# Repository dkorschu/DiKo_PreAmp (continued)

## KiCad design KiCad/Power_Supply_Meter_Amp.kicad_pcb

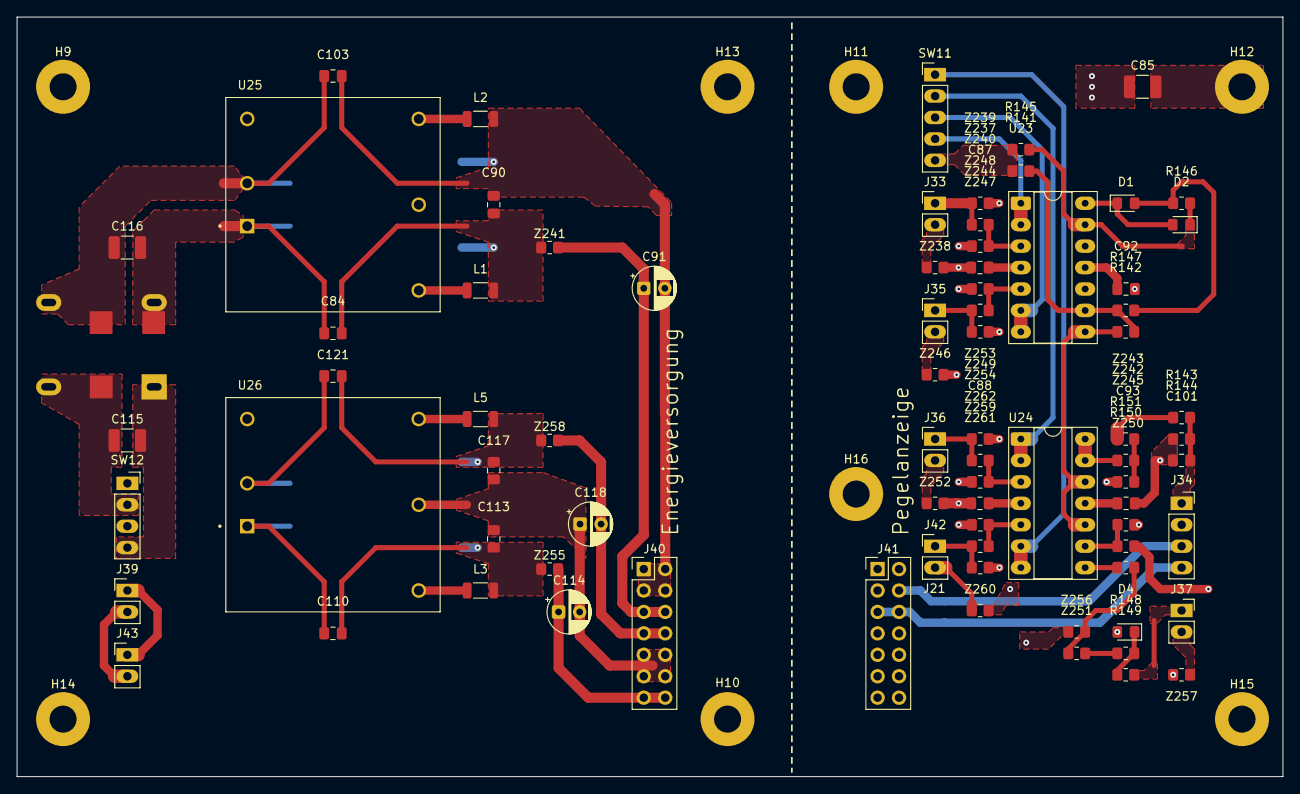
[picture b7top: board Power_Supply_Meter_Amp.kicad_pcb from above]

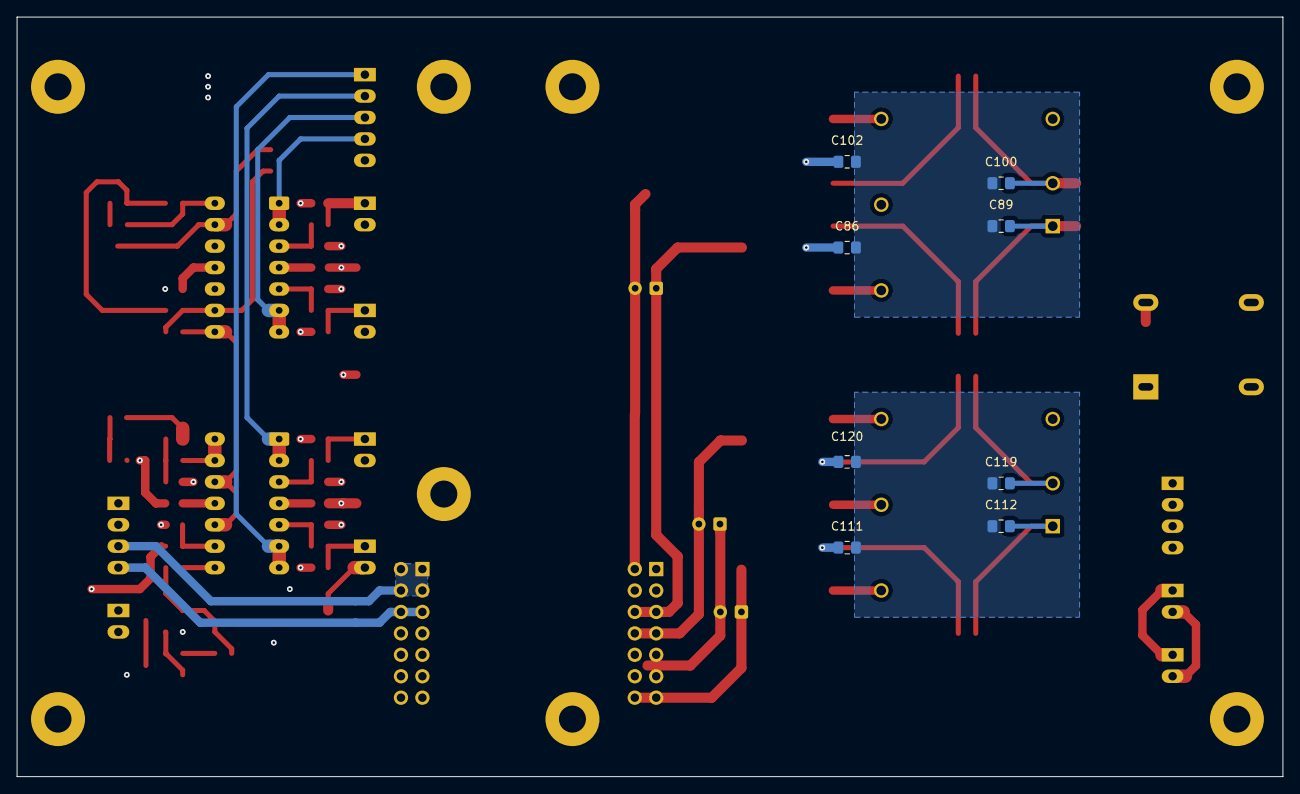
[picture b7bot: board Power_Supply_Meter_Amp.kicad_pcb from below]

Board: 4 copper layers, 150.0 x 90.0 mm, 95 parts (8 on the bottom side), 59 nets.

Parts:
C84, C103, C110, C121: 470p; C_0805_2012Metric_Pad1.18x1.45mm_HandSolder
C85: 10n; C_1210_3225Metric_Pad1.33x2.70mm_HandSolder
C86, C102, C111, C120: 1n; C_0805_2012Metric_Pad1.18x1.45mm_HandSolder
C87, C88, C90, C92, C93, C113, C117: 100n; C_0805_2012Metric_Pad1.18x1.45mm_HandSolder
C89, C100, C112, C119: 10n; C_0805_2012Metric_Pad1.18x1.45mm_HandSolder
C91, C114, C118: 10u; CP_Radial_D5.0mm_P2.50mm
C101: 4u7; C_0805_2012Metric_Pad1.18x1.45mm_HandSolder
C115, C116: 10u; C_1210_3225Metric_Pad1.33x2.70mm_HandSolder
D1, D2, D4: D; D_0805_2012Metric_Pad1.15x1.40mm_HandSolder
H9, H10, H11, H13, H14, H15, H16: MountingHole; MountingHole_3.2mm_M3_Pad
H12: MountingHole_Pad; MountingHole_3.2mm_M3_Pad
J33, J35, J36, J42: Pegel_In; PinHeader_1x02_P2.54mm_Vertical_LongPads
J34: VU_Meter_Out; PinSocket_1x04_P2.54mm_Vertical_LongPdas
J37: LED_Out; PinSocket_1x02_P2.54mm_Vertical_LongPads
J39: VCC_IN; PinHeader_1x02_P2.54mm_Vertical_LongPads
J40, J41: Conn_02x07_Odd_Even; PinHeader_2x07_P2.54mm_Vertical
J43: VCC_OUT; PinHeader_1x02_P2.54mm_Vertical_LongPads
L1, L2, L3, L5: Dämpfungsperle, 220 Ohm @ 100MHz, 0.5A; L_1206_3216Metric
L4: WE-SL575
R141: 20k; R_0805_2012Metric_Pad1.20x1.40mm_HandSolder
R142: 80k; R_0805_2012Metric_Pad1.20x1.40mm_HandSolder
R143, R144: 1k8; R_0805_2012Metric_Pad1.20x1.40mm_HandSolder
R145, R146, R149: 1k; R_0805_2012Metric_Pad1.20x1.40mm_HandSolder
R147, R148: 10k; R_0805_2012Metric_Pad1.20x1.40mm_HandSolder
R150: 12k; R_0805_2012Metric_Pad1.20x1.40mm_HandSolder
R151: 3k; R_0805_2012Metric_Pad1.20x1.40mm_HandSolder
SW11: SW_Rotary_1x4; PinHeader_1x05_P2.54mm_Vertical_LongPads
SW12: SW_DPST; PinSocket_1x04_P2.54mm_Vertical_LongPdas
U23, U24: TL074; DIP-14_W7.62mm_Socket_LongPads
U25: REC10K-2409; CONV_REC10K-2409SAW_H2
U26: REC10K-2415; CONV_REC10K-2415DAW_H2
Z237, Z238, Z239, Z240, Z241, Z242, Z243, Z244, Z245, Z246, Z247, Z248, Z249, Z250, Z251, Z252, Z253, Z254, Z255, Z256, Z257, Z258, Z259, Z260, Z261, Z262: R_0805_2012Metric_Pad1.20x1.40mm_HandSolder

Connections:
9V_GND_M: J34.3, J41.1, J41.2, J41.3, J41.4
9V_GND_P: C90.2, C91.2, C102.1, C103.2, J40.1, J40.2, J40.3, J40.4, L2.2
+9V_M: J34.4, J41.5, J41.6
+9V_P: C91.1, J40.5, J40.6, Z241.2
+15V_M: C87.2, C88.2, J41.13, J41.14, R150.1, U23.4 (V+), U24.4 (V+)
+15V_P: C114.1, J40.13, J40.14, Z255.2
-15V_M: C92.2, C93.2, J41.7, J41.8, U23.11 (V-), U24.11 (V-)
-15V_P: C118.2, J40.7, J40.8, Z258.2
/Pegel_Aux_Return: SW11.2, U24.1, U24.2 (-)
/Pegel_Mic_Effekt: SW11.3, U23.6 (-), U23.7
/Pegel_Post: SW11.1, U24.6 (-), U24.7
/Pegel_Pre: SW11.4, U23.1, U23.2 (-)
GND_9V_FILT: C86.1, C89.1, C100.2, C102.2
GND_15V_FILT: C111.1, C112.1, C119.2, C120.2
GND_M: C85.2, C87.1, C88.1, C92.1, C93.1, C101.2, D4.2 (A), J34.2, J41.9, J41.10, J41.11, J41.12, R144.1, R151.1, U23.10 (+), U23.12 (+), Z238.2, Z239.2, Z240.2, Z245.2, Z246.2, Z247.2, Z248.2, Z252.2, Z253.2, Z254.2, Z256.2, Z257.2, Z260.2, Z261.2, Z262.2
GND_P: C113.2, C114.2, C117.1, C118.1, J40.9, J40.10, J40.11, J40.12, U26.5 (COM)
unnamed: C84.2, C86.2, C90.1, L1.2, Z241.1
unnamed: C85.1, H12.1
unnamed: C110.2, C111.2, C113.1, L3.2, Z255.1
unnamed: C115.1, L4.1, SW12.4
unnamed: C115.2, L4.4, SW12.2
unnamed: C117.2, C120.1, C121.2, L5.2, Z258.1
unnamed: D1.2 (A), R146.2, R147.1
unnamed: D1.1 (K), D2.2 (A), U23.14
unnamed: D2.1 (K), R145.2, R146.1, U23.13 (-)
unnamed: D4.1 (K), R148.1, R149.2
unnamed: J33.1, Z237.1, Z239.1
unnamed: J33.2, Z238.1
unnamed: C101.1, J34.1, R143.2, R144.2
unnamed: J35.1, Z244.1, Z247.1
unnamed: J35.2, Z246.1
unnamed: J36.1, Z249.1, Z253.1
unnamed: J36.2, Z252.1
unnamed: J37.1, R149.1
unnamed: J37.2, Z257.1
unnamed: J39.1, J43.1, SW12.3
unnamed: J39.2, J43.2, SW12.1
unnamed: J42.1, Z259.1, Z261.1
unnamed: J42.2, Z260.1
unnamed: R141.1, R145.1, SW11.5
unnamed: R143.1, Z243.2
unnamed: R148.2, Z251.2
unnamed: U23.3 (+), Z237.2, Z240.1
unnamed: U23.5 (+), Z244.2, Z248.1
unnamed: R141.2, R142.1, R147.2, U23.9 (-)
unnamed: U24.8, Z250.1
unnamed: U24.3 (+), Z249.2, Z254.1
unnamed: U24.5 (+), Z259.2, Z262.1
unnamed: R142.2, U23.8, U24.10 (+), U24.12 (+)
unnamed: R150.2, R151.2, U24.9 (-)
unnamed: U24.13 (-), U24.14, Z242.1
unnamed: C84.1, C89.2, C110.1, C112.2, C116.1, L4.2, U25.1 (+VIN), U26.1 (+VIN)
unnamed: L1.1, U25.6 (+VOUT)
unnamed: C100.1, C103.1, C116.2, C119.1, C121.1, L4.3, U25.2 (-VIN), U26.2 (-VIN)
unnamed: L2.1, U25.4 (-VOUT)
unnamed: L3.1, U26.6 (+VOUT)
unnamed: L5.1, U26.4 (-VOUT)
unnamed: Z242.2, Z243.1, Z245.1
unnamed: Z250.2, Z251.1, Z256.1

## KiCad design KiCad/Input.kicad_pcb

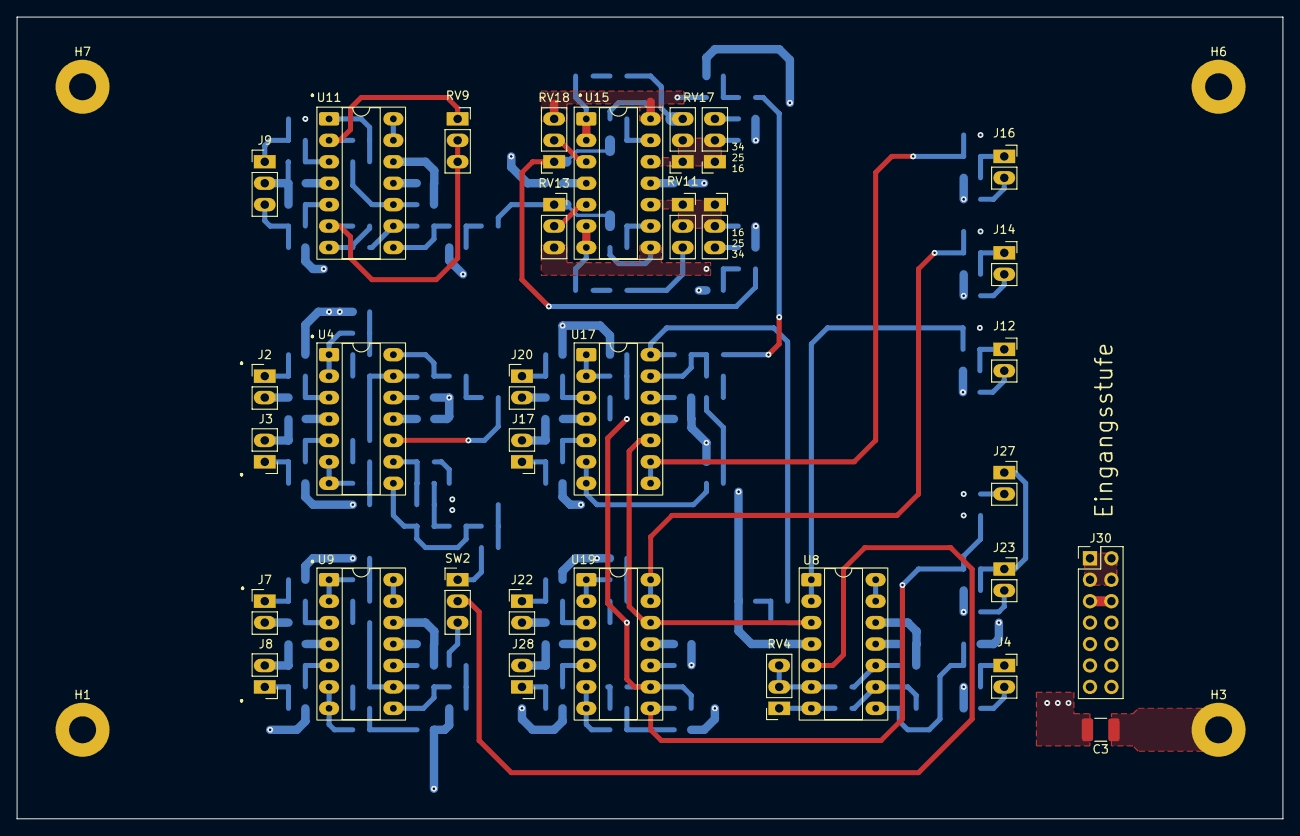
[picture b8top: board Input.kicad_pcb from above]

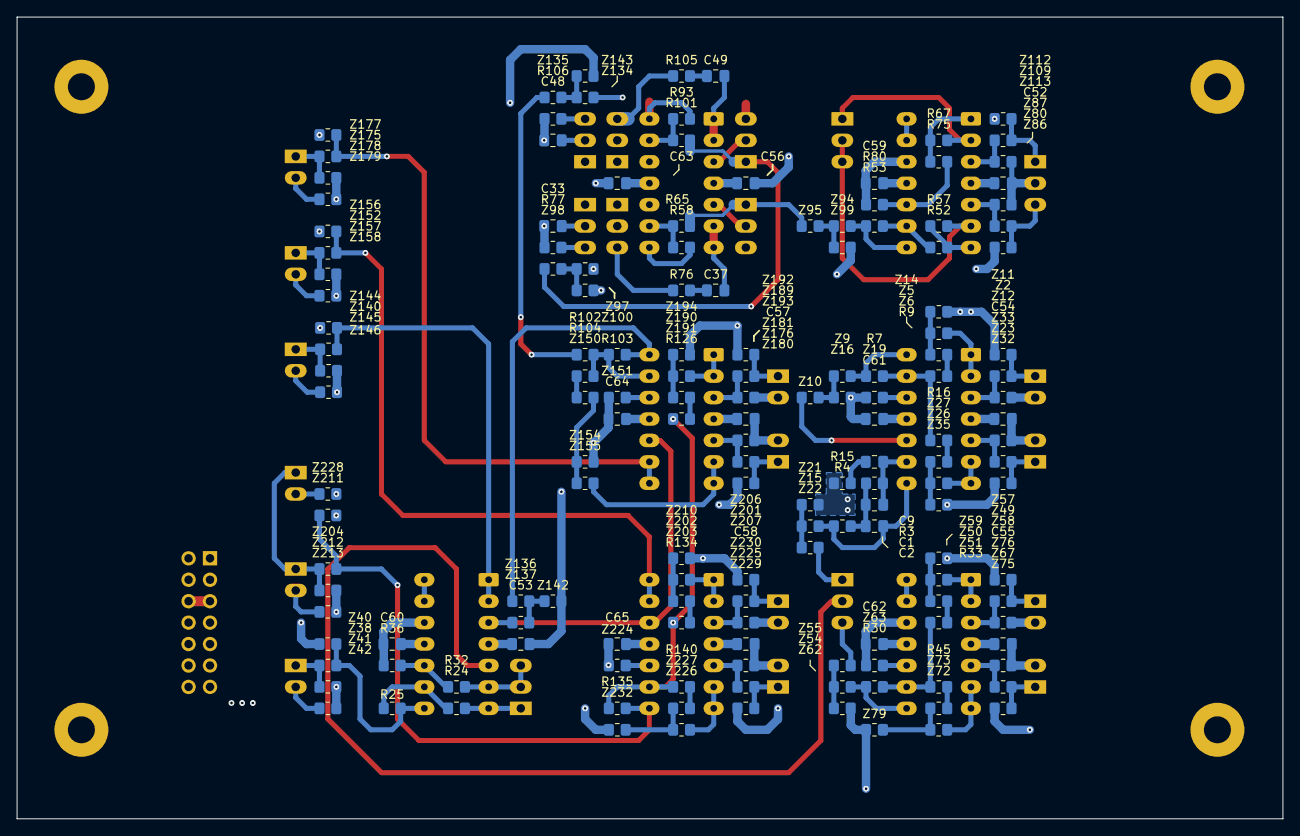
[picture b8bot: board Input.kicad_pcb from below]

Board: 4 copper layers, 150.0 x 95.0 mm, 190 parts (155 on the bottom side), 126 nets.

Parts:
C1: 2n2; C_0805_2012Metric_Pad1.18x1.45mm_HandSolder
C2: 10n; C_0805_2012Metric_Pad1.18x1.45mm_HandSolder
C3: 10n; C_1210_3225Metric_Pad1.33x2.70mm_HandSolder
C9: 47u; C_0805_2012Metric_Pad1.18x1.45mm_HandSolder
C33, C48: 470p; C_0805_2012Metric_Pad1.18x1.45mm_HandSolder
C37, C49: 3n; C_0805_2012Metric_Pad1.18x1.45mm_HandSolder
C52, C53, C54, C55, C56, C57, C58, C59, C60, C61, C62, C63, C64, C65: 100n; C_0805_2012Metric_Pad1.18x1.45mm_HandSolder
H1, H6, H7: MountingHole; MountingHole_3.2mm_M3_Pad
H3: MountingHole_Pad; MountingHole_3.2mm_M3_Pad
J2: R_Phono_In; PinHeader_1x02_P2.54mm_Vertical_LongPads
J3: L_Phono_In; PinHeader_1x02_P2.54mm_Vertical_LongPads
J4: Phono/Line_Out; PinSocket_1x02_P2.54mm_Vertical_LongPads
J7: R_Line_In; PinHeader_1x02_P2.54mm_Vertical_LongPads
J8: L_Line_In; PinHeader_1x02_P2.54mm_Vertical_LongPads
J9: Mic_In; PinHeader_1x03_P2.54mm_Vertical_LongPads
J12, J14, J16, J23, J27: Mic_Effekt_Out; PinSocket_1x02_P2.54mm_Vertical_LongPads
J17: AUX_RET_1; PinHeader_1x02_P2.54mm_Vertical_LongPads
J20: Effekt_In; PinHeader_1x02_P2.54mm_Vertical_LongPads
J22: AUX_RET_2; PinHeader_1x02_P2.54mm_Vertical_LongPads
J28: AUX_RET_3; PinHeader_1x02_P2.54mm_Vertical_LongPads
J30: Conn_02x07_Odd_Even; PinHeader_2x07_P2.54mm_Vertical
R3: 36k; R_0805_2012Metric_Pad1.20x1.40mm_HandSolder
R4: 390k; R_0805_2012Metric_Pad1.20x1.40mm_HandSolder
R7, R9, R16, R25, R30, R33, R45, R52, R53, R57, R67, R75, R80, R102, R103, R104, R126, R134, R135, R140: 10k; R_0805_2012Metric_Pad1.20x1.40mm_HandSolder
R15, R36: 1k; R_0805_2012Metric_Pad1.20x1.40mm_HandSolder
R24: 4k7; R_0805_2012Metric_Pad1.20x1.40mm_HandSolder
R32: 470R; R_0805_2012Metric_Pad1.20x1.40mm_HandSolder
R58, R65, R93, R101: 22k; R_0805_2012Metric_Pad1.20x1.40mm_HandSolder
R76, R77, R105, R106: 6k8; R_0805_2012Metric_Pad1.20x1.40mm_HandSolder
RV4: 50k log; PinSocket_1x03_P2.54mm_Vertical_LongPads
RV9: 10k lin; PinSocket_1x03_P2.54mm_Vertical_LongPads
RV11: 220k log; PinSocket_2x03_P2.54mm_Vertical_LongPads
RV13, RV18: 47k lin; PinSocket_1x03_P2.54mm_Vertical_LongPads
RV17: 220k log; PinSocket_2x03_P2.54mm_Vertical_LongPads_Mirrored
SW2: SW_SPDT; PinHeader_1x03_P2.54mm_Vertical_LongPads
U4, U8, U9, U11, U15, U17, U19: TL074; DIP-14_W7.62mm_Socket_LongPads
Z2, Z5, Z6, Z9, Z10, Z11, Z12, Z14, Z15, Z16, Z19, Z21, Z22, Z23, Z26, Z27, Z32, Z33, Z35, Z38, Z40, Z41, Z42, Z49, Z50, Z51, Z54, Z55, Z57, Z58, Z59, Z62, Z63, Z67, Z72, Z73, Z75, Z76, Z79, Z80, Z86, Z87, Z94, Z95, Z97, Z98, Z99, Z100, Z109, Z112, Z113, Z134, Z135, Z136, Z137, Z140, Z142, Z143, Z144, Z145, Z146, Z150, Z151, Z152, Z154, Z155, Z156, Z157, Z158, Z175, Z176, Z177, Z178, Z179, Z180, Z181, Z189, Z190, Z191, Z192, Z193, Z194, Z201, Z202, Z203, Z204, Z206, Z207, Z210, Z211, Z212, Z213, Z224, Z225, Z226, Z227, Z228, Z229, Z230, Z232: R_0805_2012Metric_Pad1.20x1.40mm_HandSolder

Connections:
9V_GND_I: J30.1, J30.2, J30.3, J30.4
+9V_I: J30.5, J30.6
+15V_I: C52.1, C53.2, C54.2, C55.2, C56.2, C57.2, C58.2, J30.13, J30.14, U4.4 (V+), U8.4 (V+), U9.4 (V+), U11.4 (V+), U15.4 (V+), U17.4 (V+), U19.4 (V+)
-15V_I: C59.2, C60.2, C61.2, C62.2, C63.2, C64.2, C65.2, J30.7, J30.8, U4.11 (V-), U8.11 (V-), U9.11 (V-), U11.11 (V-), U15.11 (V-), U17.11 (V-), U19.11 (V-)
GND_I: C3.2, C33.2, C48.2, C52.2, C53.1, C54.1, C55.1, C56.1, C57.1, C58.1, C59.1, C60.1, C61.1, C62.1, C63.1, C64.1, C65.1, J2.2, J3.2, J7.2, J8.2, J9.2, J17.2, J20.2, J22.2, J28.2, J30.9, J30.10, J30.11, J30.12, R15.1, R36.1, R77.1, R80.1, R106.1, U8.12 (+), U9.12 (+), U11.12 (+), Z11.2, Z12.2, Z14.2, Z16.2, Z19.2, Z21.2, Z32.2, Z33.2, Z35.2, Z40.2, Z41.2, Z42.2, Z57.2, Z58.2, Z59.2, Z62.2, Z63.2, Z75.2, Z76.2, Z79.2, Z86.2, Z87.2, Z99.2, Z100.2, Z112.2, Z113.2, Z142.2, Z143.1, Z144.2, Z145.2, Z146.2, Z151.2, Z154.2, Z156.2, Z157.2, Z158.2, Z177.2, Z178.2, Z179.2, Z180.2, Z181.2, Z192.2, Z193.2, Z194.2, Z206.2, Z207.2, Z210.2, Z211.2, Z212.2, Z213.2, Z224.2, Z228.2, Z229.2, Z230.2, Z232.2
unnamed: C1.2, C2.1, R3.1, R4.2
unnamed: C2.2, R4.1, U4.8, Z15.1
unnamed: C3.1, H3.1
unnamed: C9.1, R15.2
unnamed: C37.1, R76.1
unnamed: C49.1, R105.1
unnamed: J2.1, Z2.1, Z11.1
unnamed: J3.1, Z23.1, Z32.1
unnamed: J4.1, Z38.2, Z41.1
unnamed: J4.2, Z42.1
unnamed: J7.1, Z49.1, Z57.1
unnamed: J8.1, Z67.1, Z75.1
unnamed: J9.1, Z109.1, Z112.1
unnamed: J9.3, Z80.1, Z86.1
unnamed: J12.1, Z140.2, Z145.1
unnamed: J12.2, Z146.1
unnamed: J14.1, Z152.2, Z157.1
unnamed: J14.2, Z158.1
unnamed: J16.1, Z175.2, Z178.1
unnamed: J16.2, Z179.1
unnamed: J17.1, Z176.1, Z180.1
unnamed: J20.1, Z189.1, Z192.1
unnamed: J22.1, Z201.1, Z206.1
unnamed: J23.1, J27.1, Z204.2, Z212.1
unnamed: J23.2, Z213.1
unnamed: J27.2, Z228.1
unnamed: J28.1, Z225.1, Z229.1
unnamed: R7.2, U4.14, Z9.1
unnamed: R9.1, Z6.2
unnamed: R16.1, Z27.2
unnamed: R24.1, RV4.1, U8.7
unnamed: R25.2, U8.8, Z38.1, Z40.1
unnamed: R30.2, U9.8, Z54.1
unnamed: R33.1, Z51.2
unnamed: R45.1, Z73.2
unnamed: R52.1, R57.2, U11.7
unnamed: R53.1, U11.8, Z94.1
unnamed: R58.2, RV13.3, U15.8, Z97.1
unnamed: R65.1, RV13.1, Z95.2
unnamed: R67.1, R75.1, U11.1
unnamed: R76.2, RV11.3
unnamed: R77.2, RV11.4
unnamed: R93.2, RV18.3, U15.14, Z134.1
unnamed: R101.1, RV18.1, Z98.2
unnamed: R102.1, Z135.2
unnamed: R103.2, U17.14, Z136.1
unnamed: R104.1, Z150.1
unnamed: R105.2, RV17.3
unnamed: R106.2, RV17.4
unnamed: R126.2, Z191.2
unnamed: R134.2, Z203.2
unnamed: R135.1, U19.8, Z204.1, Z211.1
unnamed: R140.2, Z227.2
unnamed: SW2.1 (A), Z22.2
unnamed: SW2.2 (B), U8.5 (+)
unnamed: SW2.3 (C), Z55.2
unnamed: U4.3 (+), Z2.2, Z12.1
unnamed: U4.1, U4.2 (-), Z5.1
unnamed: U4.5 (+), Z23.2, Z33.1
unnamed: U4.6 (-), U4.7, Z26.1
unnamed: U4.10 (+), Z10.2
unnamed: C1.1, C9.2, R3.2, U4.9 (-)
unnamed: U4.12 (+), Z19.1
unnamed: R7.1, R9.2, R16.2, U4.13 (-)
unnamed: U8.1, U8.2 (-), Z140.1, Z144.1
unnamed: R32.1, RV4.2, RV4.3, U8.6 (-)
unnamed: R32.2, R36.2, U8.10 (+)
unnamed: R24.2, R25.1, U8.9 (-)
unnamed: U8.13 (-), U8.14
unnamed: U9.3 (+), Z49.2, Z58.1
unnamed: U9.1, U9.2 (-), Z50.1
unnamed: U9.5 (+), Z67.2, Z76.1
unnamed: U9.6 (-), U9.7, Z72.1
unnamed: U9.10 (+), Z63.1
unnamed: R30.1, R33.2, R45.2, U9.9 (-)
unnamed: U9.13 (-), U9.14
unnamed: U11.3 (+), Z109.2, Z113.1
unnamed: R67.2, RV9.1, U11.2 (-)
unnamed: U11.5 (+), Z80.2, Z87.1
unnamed: R57.1, RV9.2, RV9.3, U11.6 (-)
unnamed: R75.2, R80.2, U11.10 (+)
unnamed: R52.2, R53.2, U11.9 (-)
unnamed: U11.13 (-), U11.14
unnamed: RV18.2, U15.3 (+)
unnamed: C49.2, U15.1, U15.2 (-)
unnamed: RV13.2, U15.5 (+)
unnamed: C37.2, U15.6 (-), U15.7
unnamed: C33.1, RV11.1, RV11.2, RV11.5, RV11.6, U15.10 (+)
unnamed: R58.1, R65.2, U15.9 (-)
unnamed: C48.1, RV17.1, RV17.2, RV17.5, RV17.6, U15.12 (+)
unnamed: R93.1, R101.2, U15.13 (-)
unnamed: U17.3 (+), Z189.2, Z193.1
unnamed: U17.1, U17.2 (-), Z190.1
unnamed: U17.5 (+), Z176.2, Z181.1
unnamed: U17.6 (-), U17.7, Z155.2
unnamed: U8.3 (+), U17.10 (+), U19.12 (+), Z137.2
unnamed: U17.8, U17.9 (-), Z175.1, Z177.1
unnamed: U17.12 (+), Z151.1
unnamed: R102.2, R103.1, R104.2, U17.13 (-)
unnamed: U19.3 (+), Z201.2, Z207.1
unnamed: U19.1, U19.2 (-), Z202.1
unnamed: U19.5 (+), Z225.2, Z230.1
unnamed: U19.6 (-), U19.7, Z226.1
unnamed: U19.10 (+), Z224.1
unnamed: R126.1, R134.1, R135.2, R140.1, U19.9 (-)
unnamed: U19.13 (-), U19.14, Z152.1, Z156.1
unnamed: Z9.2, Z10.1, Z16.1
unnamed: Z5.2, Z6.1, Z14.1
unnamed: Z15.2, Z21.1, Z22.1
unnamed: Z26.2, Z27.1, Z35.1
unnamed: Z50.2, Z51.1, Z59.1
unnamed: Z54.2, Z55.1, Z62.1
unnamed: Z72.2, Z73.1, Z79.1
unnamed: Z94.2, Z95.1, Z99.1
unnamed: Z97.2, Z98.1, Z100.1
unnamed: Z134.2, Z135.1, Z143.2
unnamed: Z136.2, Z137.1, Z142.1
unnamed: Z150.2, Z154.1, Z155.1
unnamed: Z190.2, Z191.1, Z194.1
unnamed: Z202.2, Z203.1, Z210.1
unnamed: Z226.2, Z227.1, Z232.1

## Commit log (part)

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2025-09-20 3D_Print_V1
2025-09-20 Altium_V1
2025-09-20 Bachelor_Thesis_V1
2025-09-20 Blockdiagram_V1
2025-09-20 Pictures_V1
2025-09-20 Software_V1.3
2025-09-20 README_V1
2025-10-21 Datasheed
2025-10-21 KiCad
2025-10-21 README
2025-11-10 Einpflegen der Eingangsstufe
2025-11-20 Eingangsstufe update
2025-11-24 Schaltplan Update
2025-12-11 backup update
2025-12-16 Schaltplan und Blockschaltbild Update
2025-12-20 Footprint Update
2025-12-22 PCB Update
2026-01-01 PCB Update Power Supply VU Amp
2026-02-16 PCB Final Update
2026-02-19 common mode chocke Update
2026-02-24 final PCB Update
2026-03-05 Output phasen korrektur durch invertierender verstärker
2026-03-09 Output Stage in phase gebracht
2026-03-16 DRC Update
2026-03-16 Gerber Update
2026-03-22 Bezeichner und BOM Update
2026-04-02 Kicad Einstellungen
2026-04-03 Einganststufe Update
2026-04-14 RIAA Spice
2026-04-19 phono aktulisert
2026-05-03 EQ Output Update
2026-05-06 Update Outputstage
2026-05-08 Notebook update
2026-05-10 Update mit Fotos und Blockschaltbild
2026-05-11 Bass Bandpass Update
2026-05-12 update kick
2026-05-13 Mitten Update
2026-05-15 Höhen Update
2026-05-15 Finales Update Ausgangsstufe
2026-05-16 Pegel Update
2026-05-16 VU Test
2026-05-17 VU Update
2026-06-02 Erste mal musik durch geschickt
2026-06-02 Versuchsaufbau
